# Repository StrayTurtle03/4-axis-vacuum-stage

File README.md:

# ECE445_sp25 at ZJUI
Copyrights belong to ZJU-UIUC institute.  
Materials can only be used for study.  
Any violation to academic integration will not be allowed.

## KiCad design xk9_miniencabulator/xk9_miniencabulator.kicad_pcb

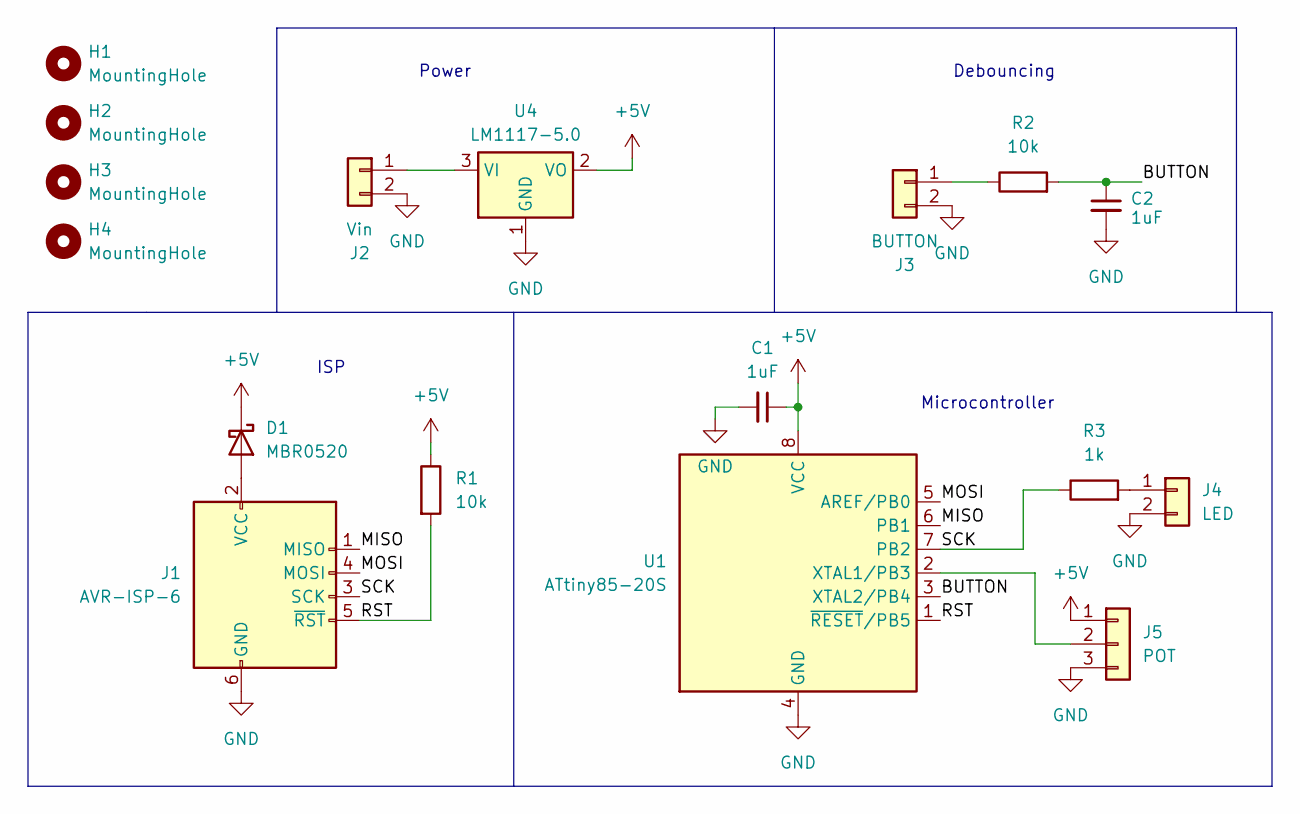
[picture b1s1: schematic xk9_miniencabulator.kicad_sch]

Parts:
C1, C2: 1uF; C_0805_2012Metric_Pad1.18x1.45mm_HandSolder
D1: MBR0520; D_SOD-123
H1, H2, H3, H4: MountingHole; MountingHole_3.2mm_M3
J1: AVR-ISP-6; IDC-Header_2x03_P2.54mm_Vertical
J2: Vin; Molex_KK-254_AE-6410-02A_1x02_P2.54mm_Vertical
J3: BUTTON; Molex_KK-254_AE-6410-02A_1x02_P2.54mm_Vertical
J4: LED; Molex_KK-254_AE-6410-02A_1x02_P2.54mm_Vertical
J5: POT; Molex_KK-254_AE-6410-03A_1x03_P2.54mm_Vertical
R1, R2: 10k; R_0805_2012Metric_Pad1.20x1.40mm_HandSolder
R3: 1k; R_0805_2012Metric_Pad1.20x1.40mm_HandSolder
U1: ATtiny85-20S; SOIC-8_5.3x5.3mm_P1.27mm
U4: LM1117-5.0; SOT-223-3_TabPin2

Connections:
+5V: C1.1, D1.1 (K), J5.1, R1.1, U1.8 (VCC), U4.2 (VO)
/BUTTON: C2.1, R2.2, U1.3 (XTAL2/PB4)
/MISO: J1.1 (MISO), U1.6 (PB1)
/MOSI: J1.4 (MOSI), U1.5 (AREF/PB0)
/RST: J1.5 (~RST), R1.2, U1.1 (~RESET/PB5)
/SCK: J1.3 (SCK), R3.1, U1.7 (PB2)
GND: C1.2, C2.2, J1.6 (GND), J2.2, J3.2, J4.2, J5.3, U1.4 (GND), U4.1 (GND)
unnamed: D1.2 (A), J1.2 (VCC)
unnamed: J2.1, U4.3 (VI)
unnamed: J3.1, R2.1
unnamed: J4.1, R3.2
unnamed: J5.2, U1.2 (XTAL1/PB3)

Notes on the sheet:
ISP
Debouncing
Power
Microcontroller

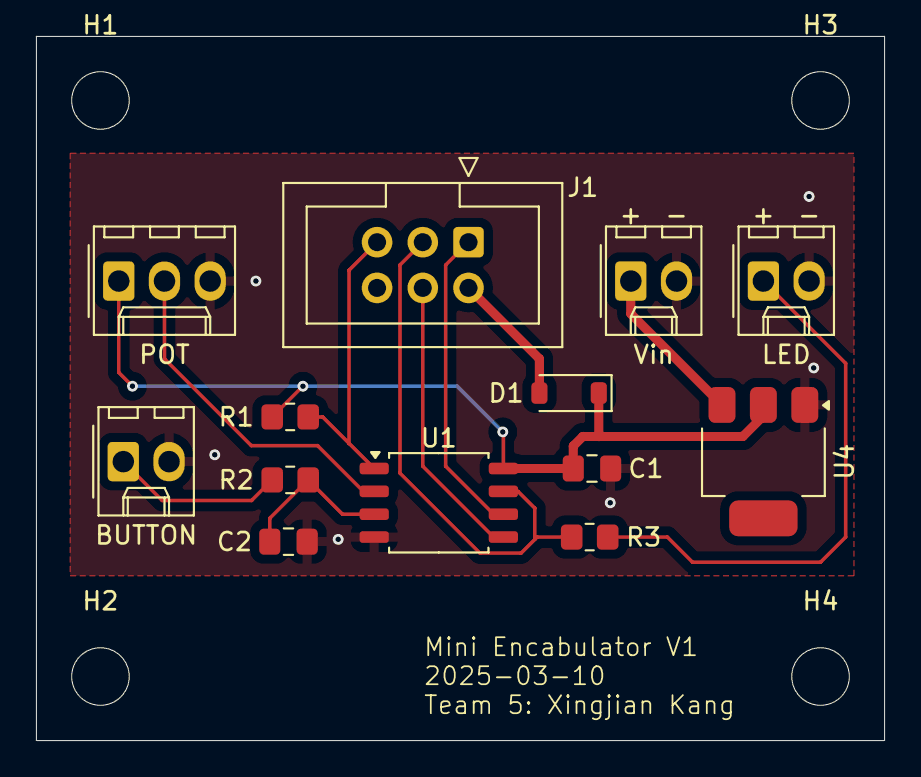
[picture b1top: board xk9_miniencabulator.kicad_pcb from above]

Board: 2 copper layers, 47.1 x 39.1 mm, 17 parts (0 on the bottom side), 12 nets.

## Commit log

2025-05-08 init
2025-05-08 add srtp files
2025-05-15 update ignore
2025-05-15 move set
2025-05-22 coating ready
2025-05-22 demo program
2025-05-22 demo r 2
